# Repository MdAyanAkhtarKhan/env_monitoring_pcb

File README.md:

# 🌱 Environmental Monitoring System (KiCad)

## 📌 Description

This project is a **PCB-based environmental monitoring system** designed using KiCad. It uses an ESP32 microcontroller to monitor **temperature, humidity, and gas levels** in real time.

Unlike basic designs, this system includes a **custom-built analog signal processing stage using LM393 comparator**, instead of relying on prebuilt sensor modules.

---

## 📷 Project Preview

---

## ⚙️ Key Design Highlight

🔹 **Custom Comparator Circuit (LM393)**

* Designed a **gas detection comparator circuit** using LM393
* Converts analog signal from MQ sensor into digital output
* Adjustable threshold using potentiometer
* Improves flexibility and understanding of analog design

---

## ⚙️ Components Used

* ESP32 Development Board
* DHT11 Sensor (Temperature & Humidity)
* MQ-6 Gas Sensor
* LM393 Comparator IC
* LCD Display (16x2 - WC1602A)
* Potentiometers (for threshold tuning)
* Resistors & Capacitors
* LED Indicator
* Power Supply Circuit

---

## 🔧 Features

* Real-time temperature and humidity monitoring
* Gas detection with adjustable sensitivity
* Custom analog comparator design (LM393)
* LCD-based output display
* Compact PCB layout

---

## 📁 Bill of Materials (BOM)

| Component             | Quantity | Description            |
| --------------------- | -------- | ---------------------- |
| ESP32 DevKit V1       | 1        | Main controller        |
| DHT11                 | 1        | Temp & humidity sensor |
| MQ-6                  | 1        | Gas sensor             |
| LM393                 | 1        | Comparator IC          |
| WC1602A LCD           | 1        | Display                |
| Resistors (2.2k, 10k) | Multiple | Biasing                |
| Capacitors (100nF)    | 2        | Filtering              |
| Potentiometers        | 2        | Threshold control      |
| LED                   | 1        | Indicator              |

---

## 🛠️ Tools Used

* KiCad (Schematic & PCB Design)
* Arduino IDE (ESP32 Programming)

---

## 🚀 Applications

* Air Quality Monitoring
* Gas Leakage Detection
* Smart Home Systems
* Industrial Safety Monitoring

---

## 🔮 Future Improvements

* IoT Cloud Integration
* Mobile App Monitoring
* Data Logging System
* Multi-sensor expansion

---

## 👨‍💻 Author

**Md Ayan Akhtar Khan**
B.Tech (ECE)

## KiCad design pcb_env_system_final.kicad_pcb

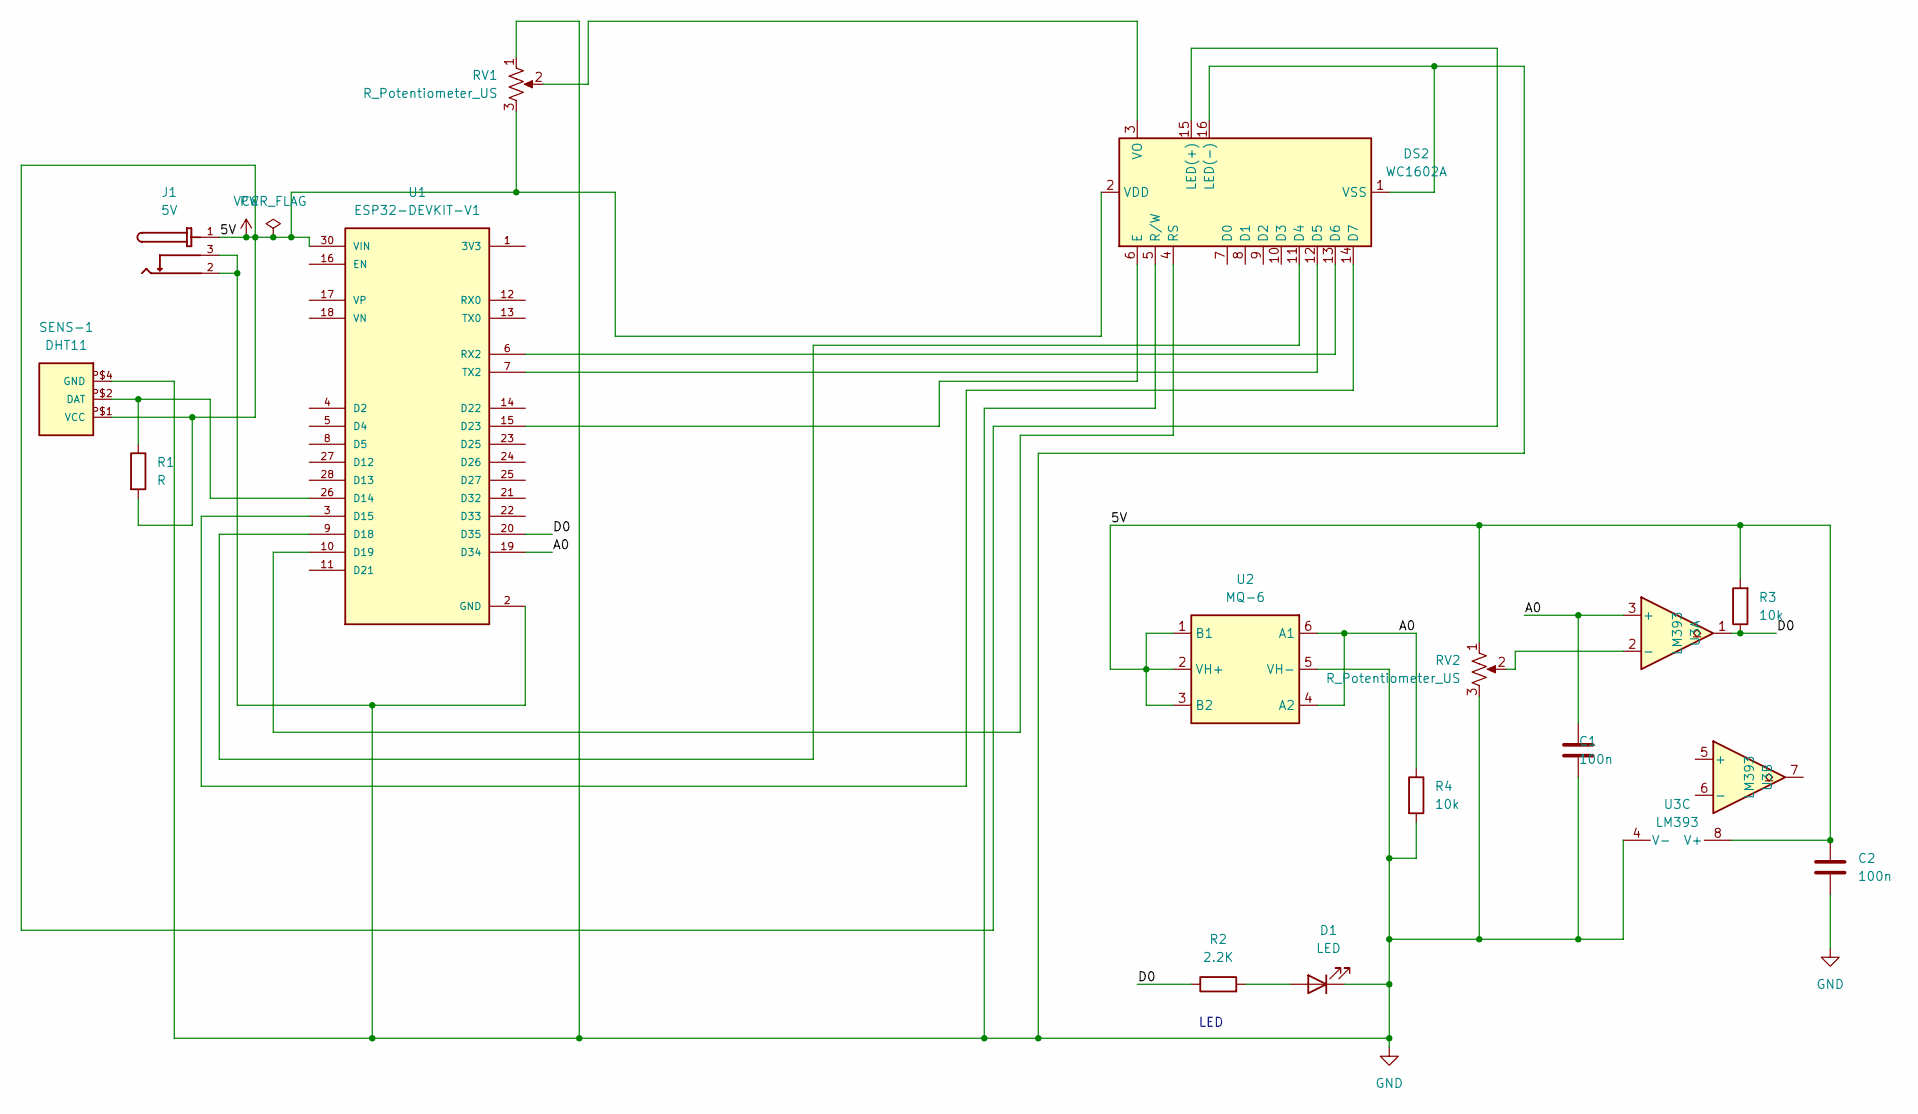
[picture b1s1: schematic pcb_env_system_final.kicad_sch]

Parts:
C1, C2: 100n; C_Disc_D5.1mm_W3.2mm_P5.00mm
D1: LED; LED_D5.0mm
DS2: WC1602A
J1: 5V; CUI_PJ-102A
R1: R; R_Axial_DIN0207_L6.3mm_D2.5mm_P10.16mm_Horizontal
R2: 2.2K; R_Axial_DIN0207_L6.3mm_D2.5mm_P10.16mm_Horizontal
R3, R4: 10k; R_Axial_DIN0207_L6.3mm_D2.5mm_P10.16mm_Horizontal
RV1, RV2: R_Potentiometer_US; Potentiometer_Bourns_3296W_Vertical
SENS-1: DHT11; SENSOR-DHT11
U1: ESP32-DEVKIT-V1; MODULE_ESP32_DEVKIT_V1; PARTREV N/A
U2: MQ-6
U3: LM393; DIP-8_W7.62mm

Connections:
/A0: C1.1, R4.1, U1.19 (D34), U2.4 (A2), U2.6 (A1), U3.3 (+)
/D0: R2.1, R3.1, U1.20 (D35), U3.1
GND: C1.2, C2.2, D1.1 (K), DS2.1 (VSS), DS2.5 (R/W), DS2.16 (LED(-)), J1.2, J1.3, R4.2, RV1.1, RV2.3, SENS-1.P$4 (GND), U1.2 (GND), U1.29 (GND), U2.5 (VH-), U3.4 (V-)
unnamed: D1.2 (A), R2.2
unnamed: DS2.11 (D4), U1.9 (D18)
unnamed: DS2.12 (D5), U1.7 (TX2)
unnamed: DS2.13 (D6), U1.6 (RX2)
unnamed: DS2.14 (D7), U1.3 (D15)
unnamed: DS2.6 (E), U1.15 (D23)
unnamed: DS2.4 (RS), U1.10 (D19)
unnamed: DS2.3 (VO), RV1.2
unnamed: R1.1, SENS-1.P$2 (DAT), U1.26 (D14)
unnamed: RV2.2, U3.2 (-)
VCC: C2.1, DS2.2 (VDD), DS2.15 (LED(+)), J1.1, R1.2, R3.2, RV1.3, RV2.1, SENS-1.P$1 (VCC), U1.30 (VIN), U2.1 (B1), U2.2 (VH+), U2.3 (B2), U3.8 (V+)

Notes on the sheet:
LED

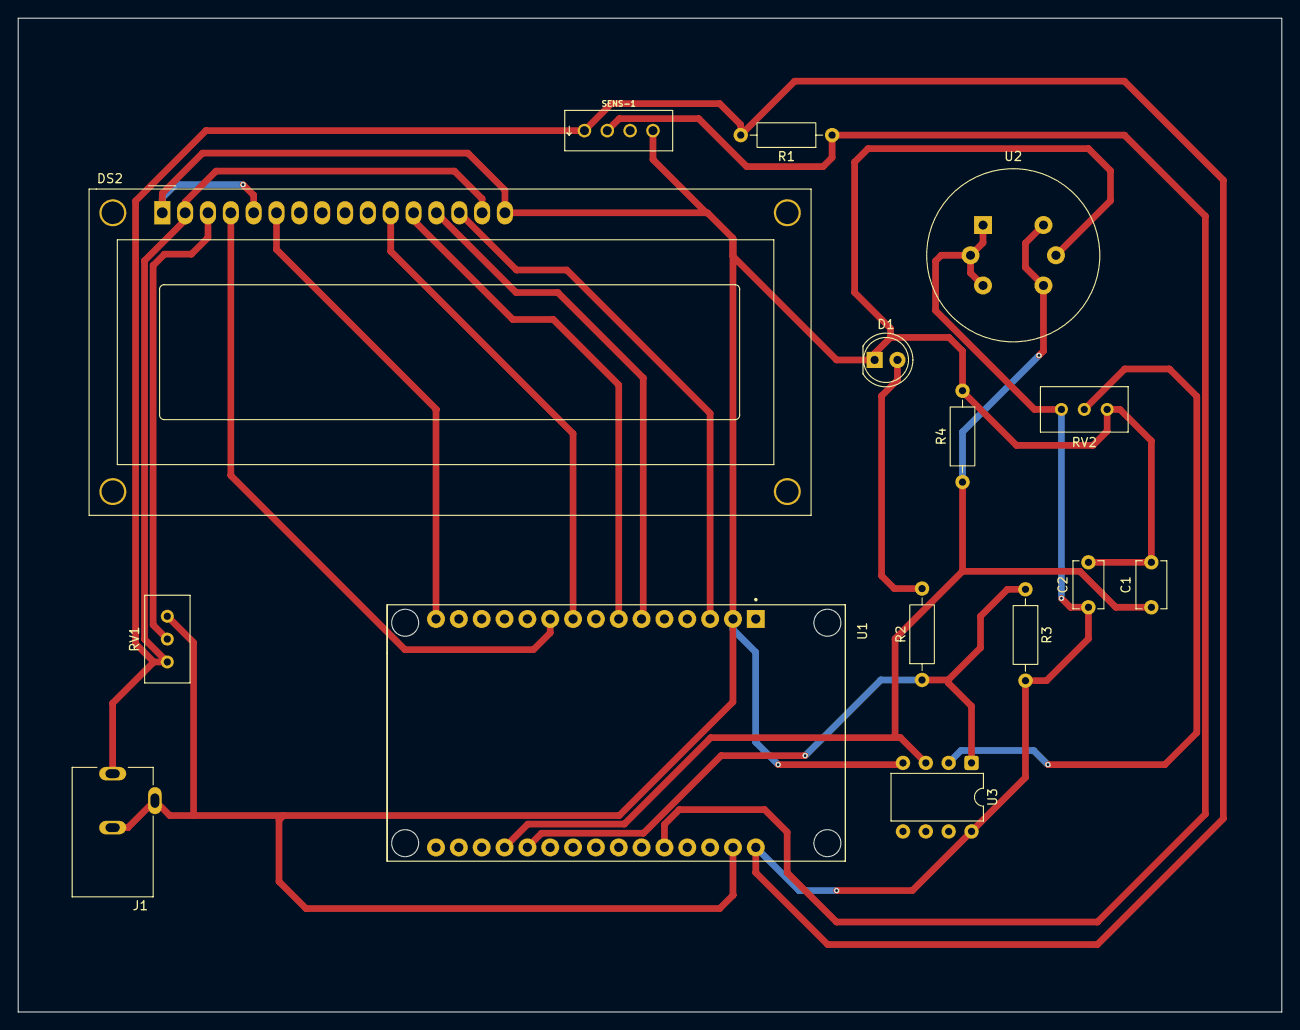
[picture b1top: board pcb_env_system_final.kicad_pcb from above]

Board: 2 copper layers, 140.5 x 110.5 mm, 15 parts (0 on the bottom side), 14 nets.

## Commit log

2026-04-08 Initialize README for Environmental Monitoring System
    Added detailed project description, features, components, tools, applications, and future improvements for the Environmental Monitoring System.
2026-04-08 Update PCB Design image format from JPG to PNG
